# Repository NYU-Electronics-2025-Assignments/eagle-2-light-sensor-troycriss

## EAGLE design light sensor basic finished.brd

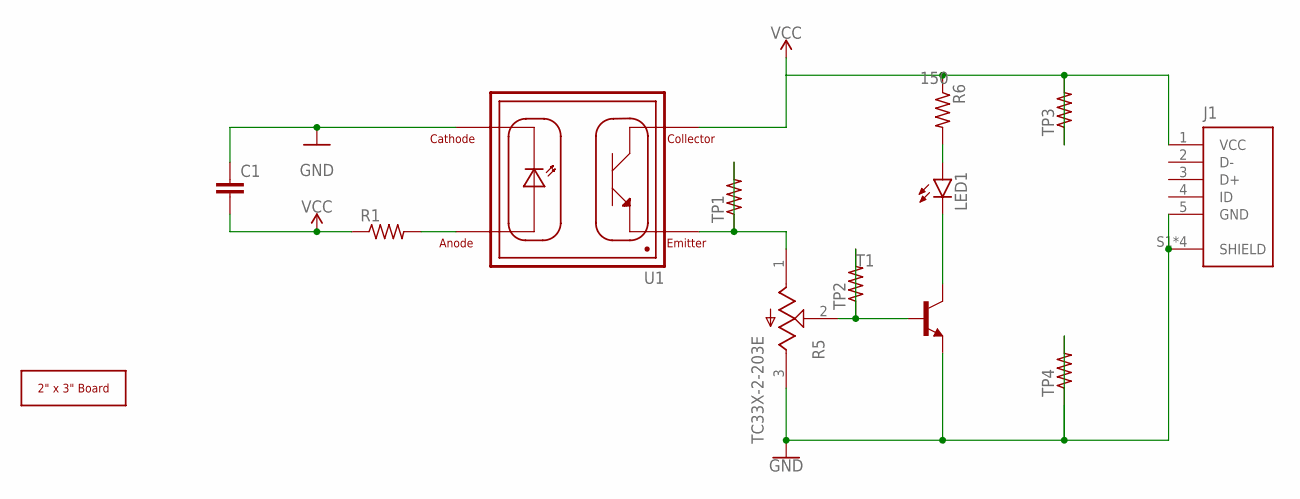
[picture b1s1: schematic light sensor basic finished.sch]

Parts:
C1: 1 uF; C1206
J1: UJ2-MIBH-G-SMT-TR; CUI_UJ2-MIBH-G-SMT-TR
LED1: LEDSML0805; SML0805
R1: R-US_M1206; M1206
R5: TC33X-2-203E; TRIM_TC33X-2-203E
R6: 150; M0805
T1: -NPN-SOT23-EBC; SOT23-EBC
TP1, TP2, TP3, TP4: R-US_M1206; M1206
U1: VCNT2020; XDCR_VCNT2020
U$1: 2X3_BOARD_V2

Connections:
GND: C1.1, J1.5 (GND), J1.S1 (SHIELD), J1.S2 (SHIELD), J1.S3 (SHIELD), J1.S4 (SHIELD), R5.3 (CW), T1.E, TP4.1, TP4.2, U1.4 (CATHODE)
unnamed: R1.2, U1.3 (ANODE)
unnamed: R5.1 (CCW), TP1.1, TP1.2, U1.1 (EMITTER)
unnamed: R5.2 (W), T1.B, TP2.1, TP2.2
unnamed: LED1.C, T1.C
unnamed: LED1.A, R6.2
VCC: C1.2, J1.1 (VCC), R1.1, R6.1, TP3.1, TP3.2, U1.2 (COLLECTOR)

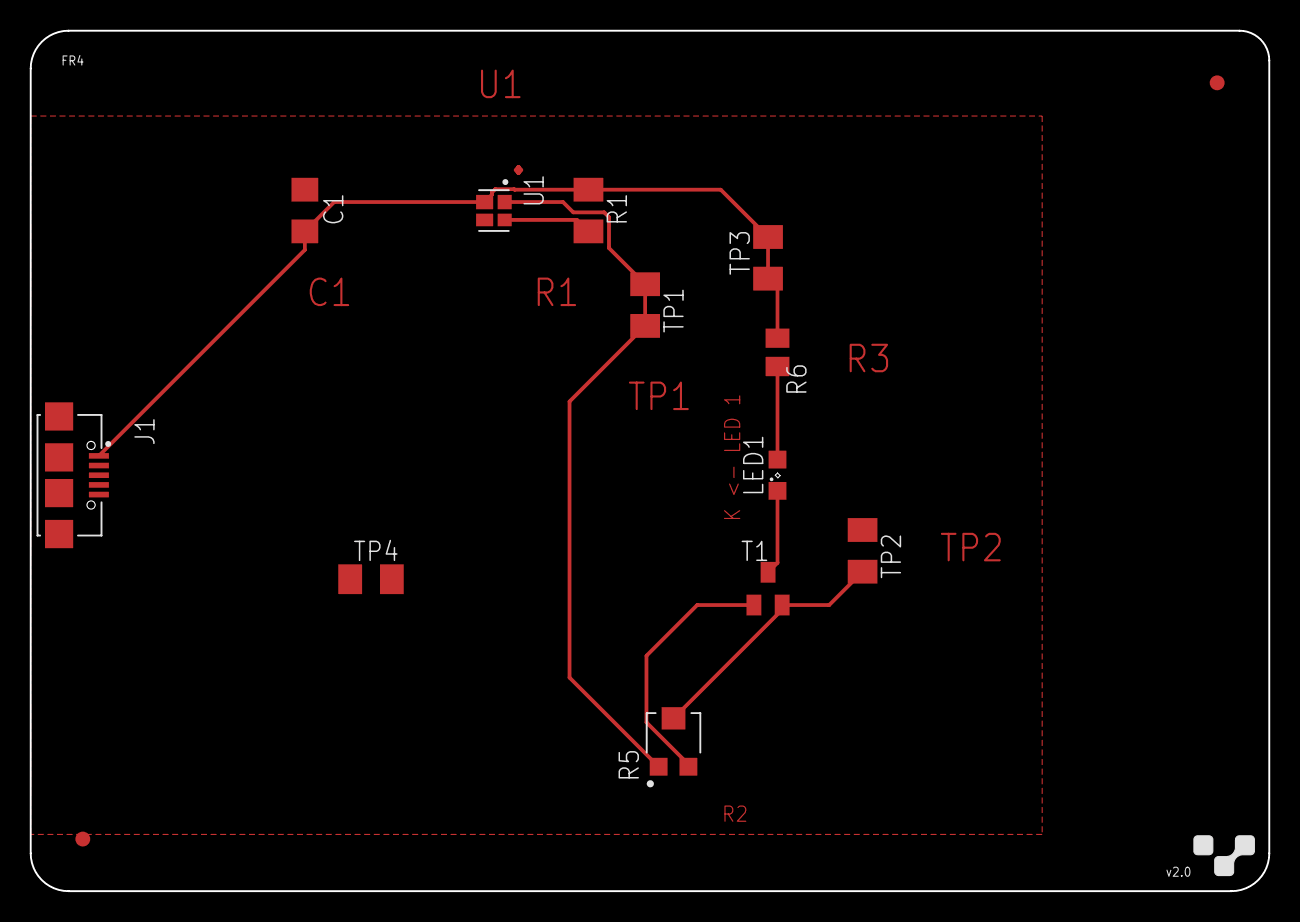
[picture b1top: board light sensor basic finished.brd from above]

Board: 2 copper layers, 83.2 x 57.8 mm, 13 parts (0 on the bottom side), 7 nets.

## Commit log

2025-03-01 Add files via upload
    Sorry I've uploaded new files again there had some difficulties on my first try with the original files.

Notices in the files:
parts and their libraries:
SparkFun-PowerSymbols: Licensing: Creative Commons ShareAlike 4.0 International - https://creativecommons.org/licenses/by-sa/4.0
